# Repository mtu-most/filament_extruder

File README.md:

<h1>MOST Filament Extruder V4.1</h1>

The MOST filament extruder for making your own filament.

<a href="https://github.com/mtu-most/most-scad-libraries">MOST SCAD libraries</a> are required if the SCAD files are used. Put all SCAD files in the same directory. The renderer provides a relatively easy way to render the parts while still allowing the extruder library to be used in other designs.

Models of all the printed parts are available in the models/stl directory and pictures of the printed parts may be found in models/rendering.

Development of the electronics was done with Kicad and all source is available in the aptly named kicad directory. Gerbers are there, too.

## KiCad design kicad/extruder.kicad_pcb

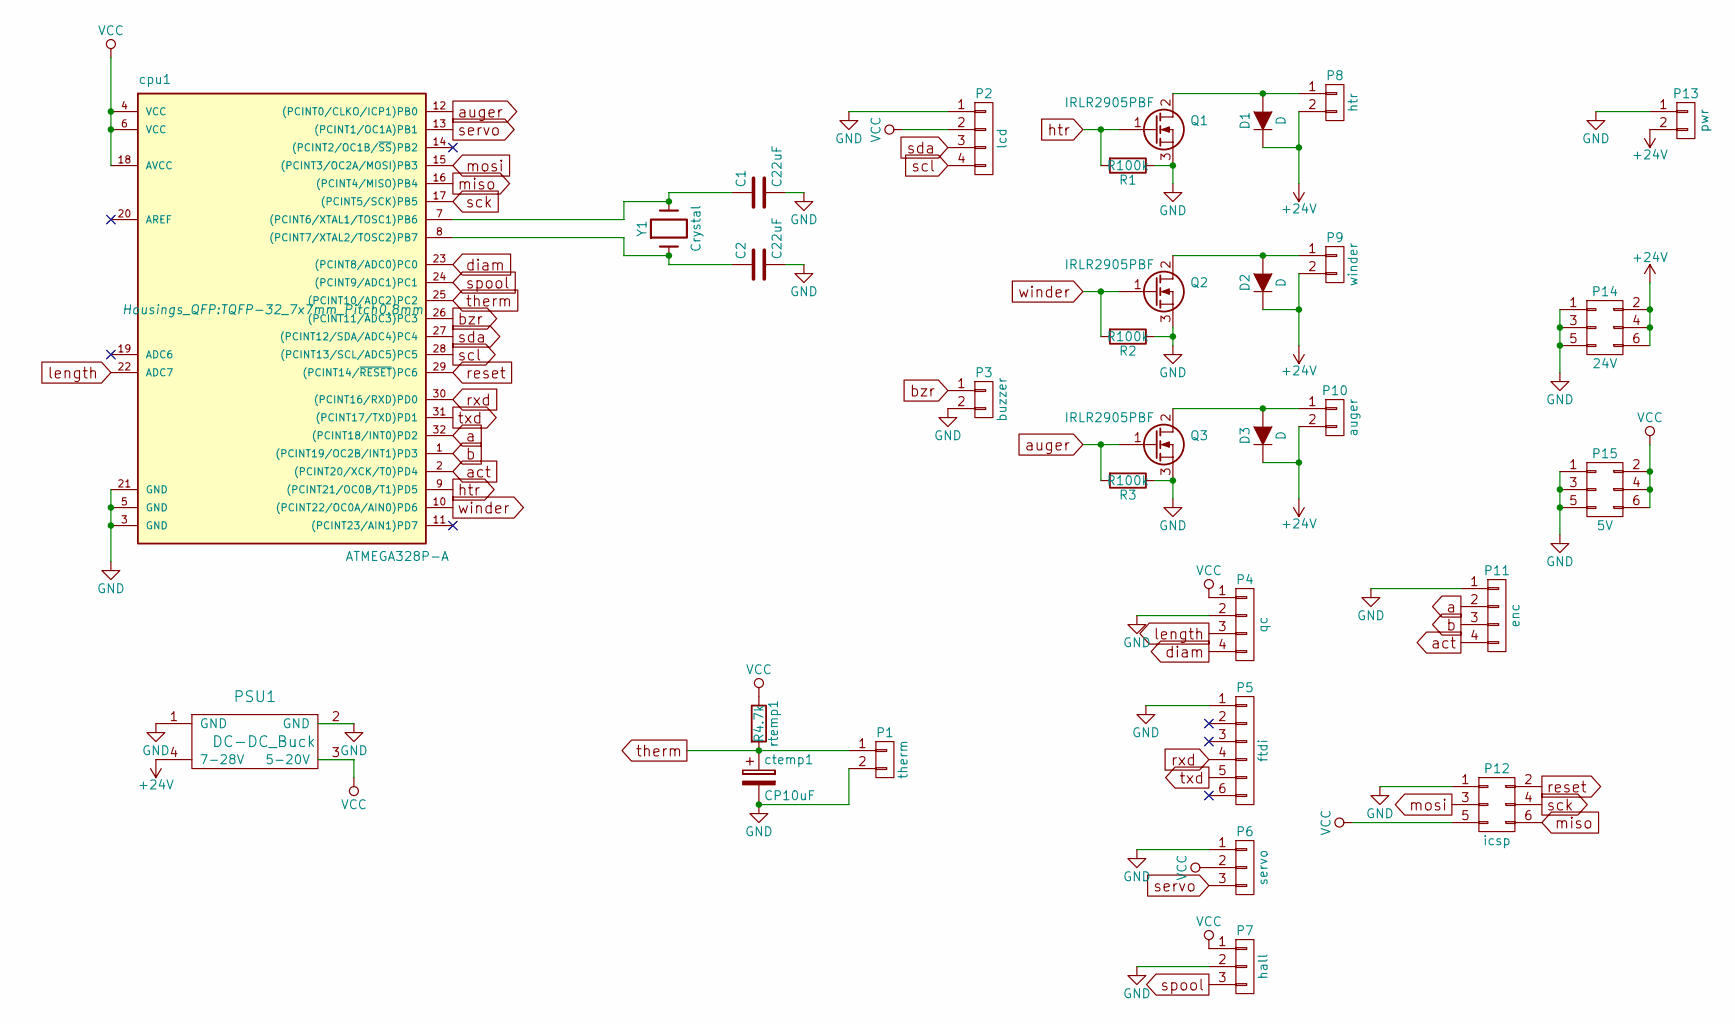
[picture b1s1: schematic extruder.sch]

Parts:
C1, C2: C22uF; C_0805
D1, D2, D3: D; DO-214AC
P1: therm; Pin_Header_Straight_1x02
P2: lcd; Pin_Header_Straight_1x04
P3: buzzer; Pin_Header_Straight_1x02
P4: qc; Pin_Header_Straight_1x04
P5: ftdi; Pin_Header_Straight_1x06
P6: servo; Pin_Header_Straight_1x03
P7: hall; Pin_Header_Straight_1x03
P8: htr; 2Screw
P9: winder; Pin_Header_Straight_1x02
P10: auger; 2Screw
P11: enc; Pin_Header_Straight_1x04
P12: icsp; Pin_Header_Straight_2x03
P13: pwr; 2Screw
P14: 24V; Pin_Header_Straight_2x03
P15: 5V; Pin_Header_Straight_2x03
PSU1: DC-DC_Buck; 7-28V
Q1, Q2, Q3: IRLR2905PBF; TO-252-2Lead
R1, R2, R3: R100k; R_0603
Y1: Crystal; Crystal_HC49-SD_SMD
cpu1: ATMEGA328P-A; TQFP-32_7x7mm_Pitch0.8mm
ctemp1: CP10uF; c_elec_3x5.3
rtemp1: R4.7k; R_1206

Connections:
+24V: D1.1 (K), D2.1 (K), D3.1 (K), P8.2, P9.2, P10.2, P13.2, P14.2, P14.4, P14.6, PSU1.4 (7-28V)
GND: C1.2, C2.2, P1.2, P2.1, P3.2, P4.2, P5.1, P6.1, P7.2, P11.1, P12.1, P13.1, P14.1, P14.3, P14.5, P15.1, P15.3, P15.5, PSU1.1 (GND), PSU1.2 (GND), Q1.3 (S), Q2.3 (S), Q3.3 (S), R1.1, R2.1, R3.1, cpu1.3 (GND), cpu1.5 (GND), cpu1.21 (GND), ctemp1.2
unnamed: C1.1, Y1.2, cpu1.7 ((PCINT6/XTAL1/TOSC1)PB6)
unnamed: C2.1, Y1.1, cpu1.8 ((PCINT7/XTAL2/TOSC2)PB7)
unnamed: D1.2 (A), P8.1, Q1.2 (D)
unnamed: D2.2 (A), P9.1, Q2.2 (D)
unnamed: D3.2 (A), P10.1, Q3.2 (D)
VCC: P2.2, P4.1, P6.2, P7.1, P12.5, P15.2, P15.4, P15.6, PSU1.3 (5-20V), cpu1.4 (VCC), cpu1.6 (VCC), cpu1.18 (AVCC), rtemp1.1
a: P11.2, cpu1.32 ((PCINT18/INT0)PD2)
act: P11.4, cpu1.2 ((PCINT20/XCK/T0)PD4)
auger: Q3.1 (G), R3.2, cpu1.12 ((PCINT0/CLKO/ICP1)PB0)
b: P11.3, cpu1.1 ((PCINT19/OC2B/INT1)PD3)
bzr: P3.1, cpu1.26 ((PCINT11/ADC3)PC3)
diam: P4.4, cpu1.23 ((PCINT8/ADC0)PC0)
htr: Q1.1 (G), R1.2, cpu1.9 ((PCINT21/OC0B/T1)PD5)
length: P4.3, cpu1.22 (ADC7)
miso: P12.6, cpu1.16 ((PCINT4/MISO)PB4)
mosi: P12.3, cpu1.15 ((PCINT3/OC2A/MOSI)PB3)
reset: P12.2, cpu1.29 ((PCINT14/~RESET~)PC6)
rxd: P5.4, cpu1.30 ((PCINT16/RXD)PD0)
sck: P12.4, cpu1.17 ((PCINT5/SCK)PB5)
scl: P2.4, cpu1.28 ((PCINT13/SCL/ADC5)PC5)
sda: P2.3, cpu1.27 ((PCINT12/SDA/ADC4)PC4)
servo: P6.3, cpu1.13 ((PCINT1/OC1A)PB1)
spool: P7.3, cpu1.24 ((PCINT9/ADC1)PC1)
therm: P1.1, cpu1.25 ((PCINT10/ADC2)PC2), ctemp1.1, rtemp1.2
txd: P5.5, cpu1.31 ((PCINT17/TXD)PD1)
winder: Q2.1 (G), R2.2, cpu1.10 ((PCINT22/OC0A/AIN0)PD6)

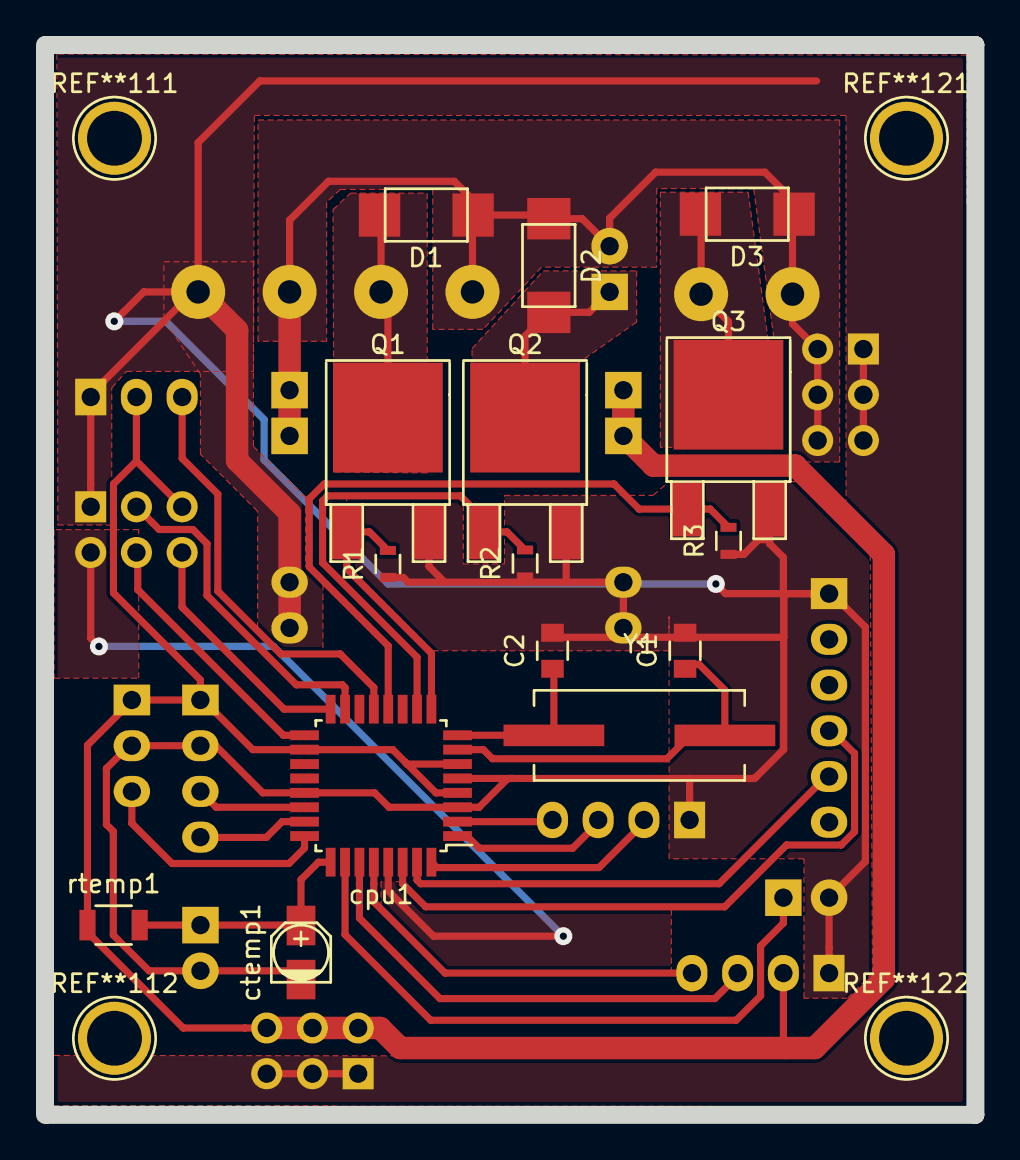
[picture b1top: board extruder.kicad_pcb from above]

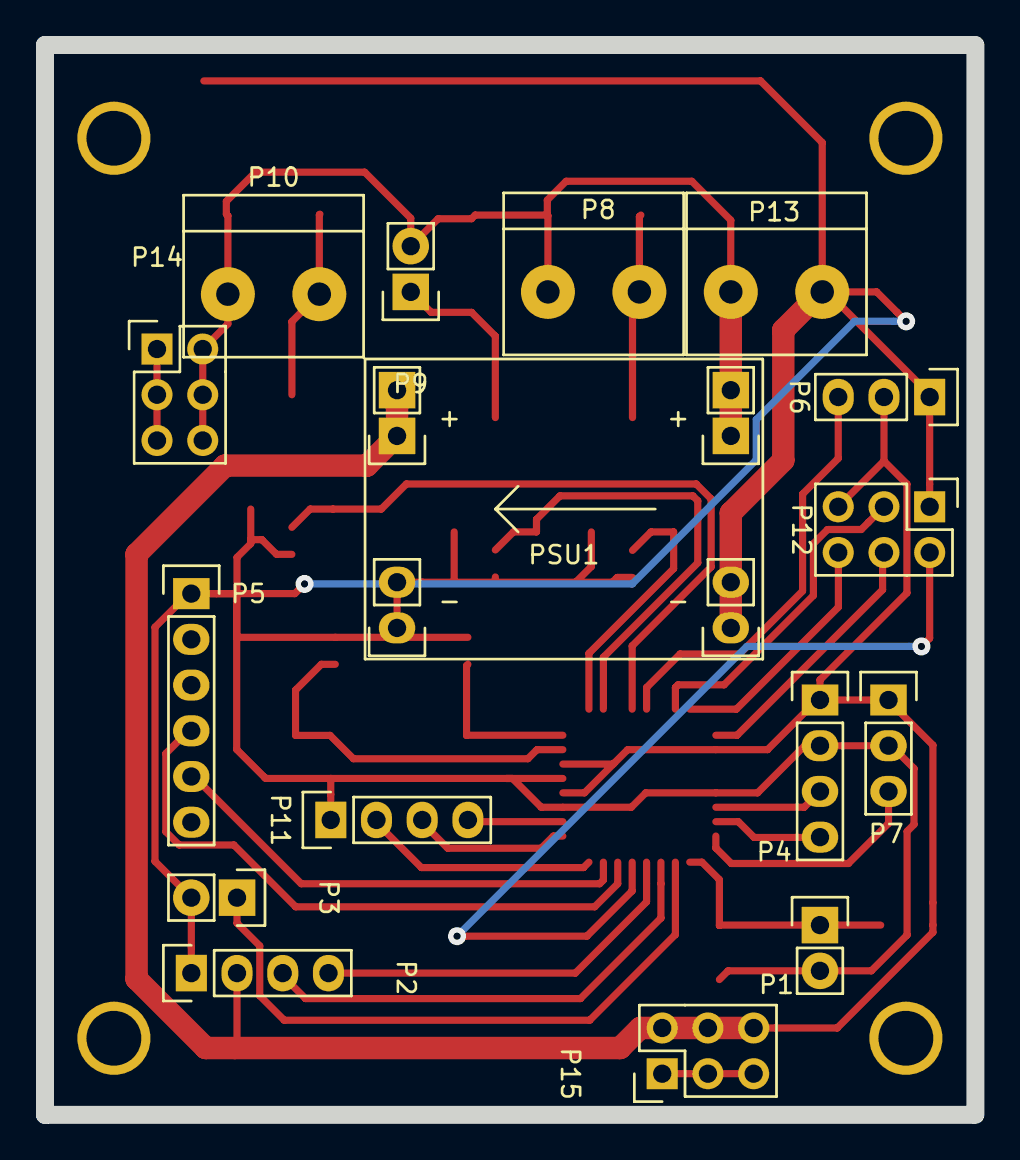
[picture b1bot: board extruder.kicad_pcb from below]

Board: 2 copper layers, 51.7 x 59.4 mm, 31 parts (16 on the bottom side), 28 nets.

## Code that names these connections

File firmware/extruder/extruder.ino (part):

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
/* Conversion between pin change interrupt numbers, port+pin pairs and arduino pin numbers: {{{
pcint	avr	pin		used as
00	B0	8		-				auger FET (this pin and/or 7)
01	B1	9		oc1a: winder FET
02	B2	10	spi ss	oc1b: guide servo		Cannot be used; is SS.
03	B3	11		spi mosi: icsp
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20	D4	4		pcint20: ui select
21	D5	5		oc0b: auger FET			guide servo
22	D6	6		oc0a: heater FET
23	D7	7		-				auger FET (this pin and/or 8)

		A6		-
		A7		QC: diameter
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// Define this as ! to invert the signal.
#define INVERT_HEATER !
	// Winder.
#define PIN_WINDER	5
#define PIN_HALL	7
#define PIN_GUIDE 	6
	// Auger motor.
#define PIN_AUGER	A1
// Define this as ! to invert the signal.
#define INVERT_AUGER !
	// QC.
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// Define this as ! to invert the signal.
#define INVERT_HEATER
	// Winder.
#define PIN_WINDER	6
#define PIN_HALL	A1
#define PIN_GUIDE 	9
	// Auger motor.
#define PIN_AUGER	8
// Define this as ! to invert the signal.
#define INVERT_AUGER
	// QC.
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		return;
	case 1:
		digitalWrite(PIN_HEATER, INVERT_HEATER(false));
		digitalWrite(PIN_AUGER, INVERT_AUGER(false));
		Serial.println("Syncing sensor");
		lcd.clear();
		lcd.print("Syncing sensor");
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		force_winder = -1;
	return BACK;
} // }}}
static Menu <4> startup_menu(	"Startup" , (char const *[]){"Toggle Heater", "Toggle Winder", "Toggle Auger", "Back"}, (action *[]){&toggle_heater, &toggle_winder, &toggle_auger, &startup_back});
//				"........#170.5°C"
// }}}

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MenuItem(qc_len_step) {	// {{{
	return edit_num(len_step, "Length Step", 0, 1000, true);
} // }}}
static Menu <5> qc_menu(	"QC"      , (char const *[]){"Report", "Dia Slope", "Dia Intercept", "Length Step", "Back"}, (action *[]){&qc_report, &qc_dia_slope, &qc_dia_intercept, &qc_len_step, &back});
//				"........#170.5°C"
#endif
// }}}
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/*********** Main functions. **************/
void setup() { // {{{
	// Before doing anything else: make sure MOSFET inputs are not floating.
	pinMode(PIN_WINDER, OUTPUT);
	digitalWrite(PIN_WINDER, LOW);
	pinMode(PIN_AUGER, OUTPUT);
	digitalWrite(PIN_AUGER, INVERT_AUGER(false));
	pinMode(PIN_HEATER, OUTPUT);
	digitalWrite(PIN_HEATER, INVERT_HEATER(false));

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			last_temp_update += 100;
	}
	// Winder.
	analogWrite(PIN_WINDER, handle_winder());
	handle_guide();
	// Auger motor.
	digitalWrite(PIN_AUGER, INVERT_AUGER(run_auger));
	// QC.
	update_len();
	// Report once per second.
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
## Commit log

2016-02-25 added kicad
2016-03-16 updated schematic
2016-04-05 updated scads
2016-04-05 new sensor mount
2016-04-12 fixed bom
2016-04-13 updated electronics
2016-04-13 added sensor board
2016-04-13 added cad
2016-04-13 fixed renderings
2016-04-13 updated scad and fixed renderings again
2016-04-13 added stl modles
2016-04-14 added gerbers
2016-04-15 updated scad
2016-04-15 updated feed chute
2016-04-15 updated BOM for new feed chute
2016-04-18 added electronics BOMs
2016-04-19 add firmware
2016-04-21 add sensor-spy
2016-04-21 use better defaults; use a defined for sending max value

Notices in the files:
firmware/extruder/extruder.ino:
vim: set foldmethod=marker filetype=cpp :
Copyright 2015 Michigan Technological University {{{
It is released under CC-BY-3.0
If you do not have a copy of the license, it may be found at: http://creativecommons.org/licenses/by/3.0/legalcode
